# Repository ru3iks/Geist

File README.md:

<div align="center">

# GEIST

**A reference-grade balanced USB DAC, real-time DSP engine, and tactile media controller — designed and built from scratch.**

`ESP32-S3` · `PCM5102A` · `OPA1656` · `Rust` · `Tauri`

---

*24-bit · 96kHz · Balanced 4.4mm Pentaconn · 10-Band Parametric EQ · FFT Visualizer*

</div>

---

## What is Geist?

Geist is an open-source USB audio device that I designed from the ground up — the circuit, the PCB, the firmware, and the companion app. It plugs into a computer over USB-C and serves three functions simultaneously:

1. **Reference-Grade USB DAC** — Enumerates as a class-compliant USB Audio device (UAC1). Receives lossless 24-bit/96kHz audio, converts it through a hardware DAC, and drives headphones through a true balanced amplifier stage.

2. **Real-Time DSP Engine** — A 10-band parametric EQ processes audio in real-time on the ESP32-S3's vector DSP unit. An FFT spectrum visualizer renders live on the onboard display.

3. **Tactile Media Controller** — Physical rotary encoder, mechanical buttons, and a toggle switch send HID commands back to the PC for volume and playback control. No drivers needed.

The companion desktop app (built in Rust + Tauri) pushes track metadata and album art to the device, provides a graphical EQ editor, and displays real-time audio analysis.

> This project was built as a 2nd year B.Tech ECE student at Manipal Institute of Technology. Every part of it — analog circuit design, mixed-signal PCB layout, embedded Rust firmware, and desktop application — was learned and implemented from scratch.

---

## Hardware Architecture

### The Signal Chain

```
  USB-C ──► AP2112K (3.3V LDO) ──► ESP32-S3 ──► PCM5102A DAC ──► 2× OPA1656 ──► Headphones
       └──► LM27762 (±4.5V Charge Pump) ─────────────────────────────┘
```

Every component was selected to serve a specific role in the audio path:

| Block | Component | Role |
|---|---|---|
| **Power (Digital)** | AP2112K-3.3 | LDO regulator — steps 5V USB to clean 3.3V for all digital logic |
| **Power (Analog)** | LM27762 | Bipolar charge pump — generates ±4.5V dual rails for the op-amps |
| **Digital Brain** | ESP32-S3-WROOM-1 | Dual-core 240MHz processor — USB audio streaming, DSP, UI control |
| **DAC** | PCM5102A | 32-bit delta-sigma DAC — converts I2S digital audio to analog |
| **Amplifiers** | 2× OPA1656 | Ultra-low-noise dual op-amps — buffers and creates balanced output |
| **Display** | ST7789 (240×240) | SPI LCD — track info or FFT visualizer |
| **Input** | Alps EC11 + 3 push buttons + SPDT toggle | Volume/nav encoder, media keys, mode switch |
| **Output** | 4.4mm Pentaconn + 3.5mm TRS | True balanced and single-ended headphone outputs |

### The Life of an Audio Sample

This table traces a single sample from the moment it leaves the PC to the moment it moves air:

```
Step   Location                  Signal State                        Domain
─────────────────────────────────────────────────────────────────────────────
 1     PC audio engine           24-bit integer: 0x3FFFFF            Software
 2     USB cable (D+/D-)         NRZI-encoded differential packet    Digital
 3     ESP32 USB DMA buffer      Bytes in RAM                        Digital
 4     ESP32 I2S peripheral      Serial bitstream at 3.072 MHz       Digital (3.3V)
 5     PCM5102A delta-sigma      1-bit stream at 6.144 MHz           Digital
 6     PCM5102A OUTL pin         +2.05V (audio + 1.55V DC bias)      Analog
 7     OPA1656 buffer output     +2.05V → OUT_L+ (hot phase)         Analog
 8     OPA1656 inverter output   −0.50V → OUT_L− (cold phase)        Analog
 9     After 10Ω resistors       +2.04V / −0.49V                     Analog
 10    Headphone driver          ΔV = 2.53V differential → sound     Acoustic
```

### Why Balanced?

A balanced signal carries audio on two wires moving in opposite directions. Any noise that couples into the cable appears equally on both wires and is cancelled by subtraction at the receiver:

```
Single-Ended:                      Balanced:
Signal ── ╱╲╱~~╲╱╲ ── +V+noise     HOT  ── ╱╲╱~~╲╱╲ ── +V+noise
Ground ── ──────── ── 0V            COLD ── ╲╱╲~~╱╲╱ ── −V+noise

Amp sees: signal + noise            Amp subtracts: (+V+noise) − (−V+noise)
→ noise passes through ✗            = 2V signal, noise cancelled ✓
```

The OPA1656 op-amps create this balanced pair — one half buffers the DAC output (positive phase), the other half inverts it (negative phase, gain = −1).

---

## PCB Design Philosophy

Geist is laid out on a **2-layer PCB** with strict attention to analog/digital noise isolation:

```
◄──── DIGITAL ZONE ──────────►│◄──────── ANALOG ZONE ──────────►

┌──────────┐  ┌──────────────┐ │  ┌───────────┐  ┌───────────┐
│ ESP32-S3 │  │ Display,     │ │  │ OPA1656×2 │  │ Audio     │
│          │  │ Encoder,     │ │  │           │  │ Jacks     │
│          │  │ Buttons      │ │  │           │  │           │
└──────────┘  └──────────────┘ │  └───────────┘  └───────────┘
                               │
                         ┌─────┴─────┐
                         │ PCM5102A  │ ← sits on the border
                         └───────────┘

Bottom layer: UNBROKEN ground copper pour — no splits.
```

### Key Layout Rules

- **Zonal Segregation** — All digital components (ESP32, display, buttons) on one side. All analog components (op-amps, output jacks) on the other. The PCM5102A sits on the boundary with its digital input pins facing left and analog outputs facing right.

- **Solid Ground Plane** — No split grounds. A single unbroken copper pour on the bottom layer allows return currents to flow directly beneath their source traces (path of least inductance), minimizing loop area and radiated noise. This is the modern best practice endorsed by TI, Analog Devices, and EMC engineers — not the outdated "split and bridge" approach.

- **Tight Decoupling** — Every bypass capacitor is placed physically touching the power pins of its parent IC. A decoupling cap 15mm away is electrically useless — the trace inductance defeats its purpose.

- **Antenna Isolation** — The ESP32's Wi-Fi/Bluetooth antenna overhangs the board edge with a keepout zone beneath it. No copper, no traces, no components under the antenna.

---

## Firmware Architecture

The firmware is written in **Rust** using the Embassy async runtime — bare-metal, no RTOS, no garbage collector.

```
geist-firmware/
├── src/
│   ├── main.rs                ← Embassy entry, spawns all tasks
│   ├── usb/
│   │   ├── descriptors.rs     ← USB composite device (UAC1 + HID + CDC)
│   │   ├── audio.rs           ← Isochronous audio reception, buffer management
│   │   ├── hid.rs             ← Media key HID reports
│   │   └── cdc.rs             ← Serial link to companion app
│   ├── audio/
│   │   ├── i2s.rs             ← I2S DMA driver for PCM5102A
│   │   ├── buffer.rs          ← Lock-free ring buffer (USB → I2S)
│   │   └── dsp.rs             ← Biquad EQ engine + FFT analysis
│   ├── ui/
│   │   ├── display.rs         ← ST7789 SPI driver
│   │   ├── encoder.rs         ← EC11 rotary encoder with debounce
│   │   ├── buttons.rs         ← Debounced media buttons
│   │   └── renderer.rs        ← Track info view + spectrum visualizer
│   └── app/
│       └── state.rs           ← Global state machine
```

### USB Composite Device

Geist enumerates as three USB interfaces simultaneously — no custom drivers required:

| Interface | USB Class | Function |
|---|---|---|
| Audio Control + Audio Streaming | UAC1 | Appears as a sound card — receives PCM audio from the OS |
| HID (Consumer Control) | HID | Sends media keys (play/pause/next/prev) and volume from the encoder |
| CDC ACM | CDC | Virtual serial port for companion app communication |

### Real-Time DSP

The 10-band parametric EQ runs as a chain of biquad filters — each band is 5 multiplies and 4 adds per sample:

```rust
// One EQ band — runs for every sample, every channel
fn process(&mut self, x: f32) -> f32 {
    let y = self.b0 * x + self.b1 * self.x1 + self.b2 * self.x2
          - self.a1 * self.y1 - self.a2 * self.y2;
    self.x2 = self.x1; self.x1 = x;
    self.y2 = self.y1; self.y1 = y;
    y
}
```

At 48kHz stereo with 10 bands, this amounts to ~5 million operations per second — less than 2% of the ESP32-S3's capacity. The biquad coefficients are computed by the companion app from human-readable parameters (frequency, gain, Q) and sent over the CDC serial link.

### Task Model

```
Core 0 (Real-time audio — never blocked):
├── usb_audio_task()       ← Isochronous USB reception
├── i2s_feed_task()        ← Drains ring buffer → I2S DMA → PCM5102A
└── usb_hid_cdc_task()     ← HID reports + serial I/O

Core 1 (UI + DSP — lower priority):
├── dsp_task()             ← Biquad EQ processing + FFT analysis
├── display_task()         ← ST7789 rendering @ 30fps
└── input_task()           ← Encoder + button polling + debounce
```

---

## Companion App

Built with **Tauri** (Rust backend + web frontend) — a ~5MB native app, not a 150MB Electron wrapper.

### Features

- **Now Playing** — Reads track info from the OS media session (Windows SMTC / macOS MediaRemote / Linux MPRIS2) and pushes title, artist, and album art to Geist's display over CDC serial
- **10-Band Parametric EQ** — Interactive frequency response curve editor. Drag bands to set frequency, gain, and Q. Coefficients are computed locally and sent to the ESP32 in real-time
- **Real-Time Visualizer** — Captures system audio via loopback and renders spectrum analyzer, waveform, and spectrogram views in the browser frontend
- **Device Dashboard** — Connection status, sample rate, firmware version, output mode
- **System Tray** — Runs silently in the background, auto-connects when Geist is plugged in
- **Firmware Update** — Flash new firmware to the ESP32 over USB without opening the case
- **Listening Stats** — Tracks hours, volume levels, and session history in a local SQLite database

### Tech Stack

| Layer | Technology |
|---|---|
| Backend | Rust (serialport, windows-rs, cpal, rustfft, rusqlite) |
| Frontend | Svelte + HTML5 Canvas for visualizations |
| Framework | Tauri v2 |
| Protocol | JSON messages + binary RGB565 art over CDC serial |

---

## Bill of Materials

| Component | Part Number | Quantity | Description |
|---|---|---|---|
| MCU | ESP32-S3-WROOM-1 | 1 | Dual-core 240MHz, USB OTG, vector DSP |
| DAC | PCM5102A (PWR) | 1 | 32-bit delta-sigma, I2S input, 112dB SNR |
| Op-Amp | OPA1656IDR | 2 | Ultra-low-noise dual op-amp, 2.8 nV/√Hz |
| LDO | AP2112K-3.3TRG1 | 1 | 3.3V, 600mA, low-dropout regulator |
| Charge Pump | LM27762DSSR | 1 | Bipolar ±output from single supply |
| USB Connector | USB-C 16-pin | 1 | PCB-mount receptacle |
| Display | ST7789 240×240 | 1 | SPI TFT LCD module |
| Encoder | Alps EC11 | 1 | Rotary encoder with push switch |
| Toggle | SPDT | 1 | Mode select switch |
| Buttons | Tactile push | 3 | Prev / Play-Pause / Next |
| Balanced Jack | 4.4mm Pentaconn | 1 | Panel-mount, 5-pole |
| SE Jack | 3.5mm TRS | 1 | Panel-mount, 3-pole |
| Resistors | 0805 | 15 | Various values (see schematic) |
| Capacitors | 0805 | 15 | 0.1µF, 2.2µF, 4.7µF, 10µF |

---

## Project Structure

```
Geist/
├── hardware/                    ← KiCad project
│   ├── Geist.kicad_pro
│   ├── Geist.kicad_sch          ← Schematic
│   ├── Geist.kicad_pcb          ← PCB layout
│   └── fabrication/             ← Gerber files for manufacturing
│
├── firmware/                    ← ESP32-S3 Rust firmware
│   ├── Cargo.toml
│   └── src/
│
├── companion/                   ← Tauri desktop app
│   ├── src-tauri/               ← Rust backend
│   ├── src/                     ← Svelte frontend
│   └── package.json
│
├── enclosure/                   ← 3D-printable case (STEP/STL)
│
├── docs/
│   ├── hardware-signal-trace.md ← Complete electrical signal walkthrough
│   └── usb-audio-architecture.md← USB Audio Class deep dive
│
└── README.md
```

---

## Design Specifications

| Parameter | Value |
|---|---|
| Audio Format | PCM, 24-bit, 48kHz / 96kHz |
| USB Class | UAC1 (class-compliant, driverless) |
| DAC SNR | 112 dB (A-weighted) |
| DAC THD+N | −93 dB |
| Amp Noise | 2.8 nV/√Hz |
| Amp THD+N | −132 dB (0.000025%) |
| Output (Balanced) | 4.4mm Pentaconn, ~4 Vrms differential |
| Output (SE) | 3.5mm TRS |
| DSP | 10-band parametric EQ (biquad IIR) |
| Visualization | 1024-point FFT, real-time spectrum |
| Power | USB bus-powered (5V, <500mA) |
| PCB | 2-layer, solid ground plane |
| Firmware | Rust + Embassy (bare-metal async) |
| Companion App | Rust + Tauri + Svelte |

---

## Building

> 🚧 Build instructions will be added as each subsystem is completed.

### Hardware
1. Open `hardware/Geist.kicad_pro` in KiCad 9.0+
2. Generate Gerbers and order from JLCPCB or PCBWay (2-layer, 1.6mm, 1oz copper)
3. Source components from LCSC/Mouser/Digikey (see BOM above)
4. Hand-solder with hot air station (TSSOP/QFN packages) and soldering iron (0805 passives, connectors)

### Firmware
```bash
# Prerequisites: Rust toolchain + ESP32 target
rustup target add xtensa-esp32s3-none-elf
cargo install espflash

# Build and flash
cd firmware
cargo build --release
espflash flash target/xtensa-esp32s3-none-elf/release/geist-firmware
```

### Companion App
```bash
# Prerequisites: Rust, Node.js 18+, pnpm
cd companion
pnpm install
pnpm tauri dev     # development
pnpm tauri build   # production binary
```

---

## License

This project is open-source under the [MIT License](LICENSE).

---

<div align="center">

Designed and built by **Arihant** · MIT Manipal · 2026

*A project born from curiosity about what sits between the music and the ear.*

</div>

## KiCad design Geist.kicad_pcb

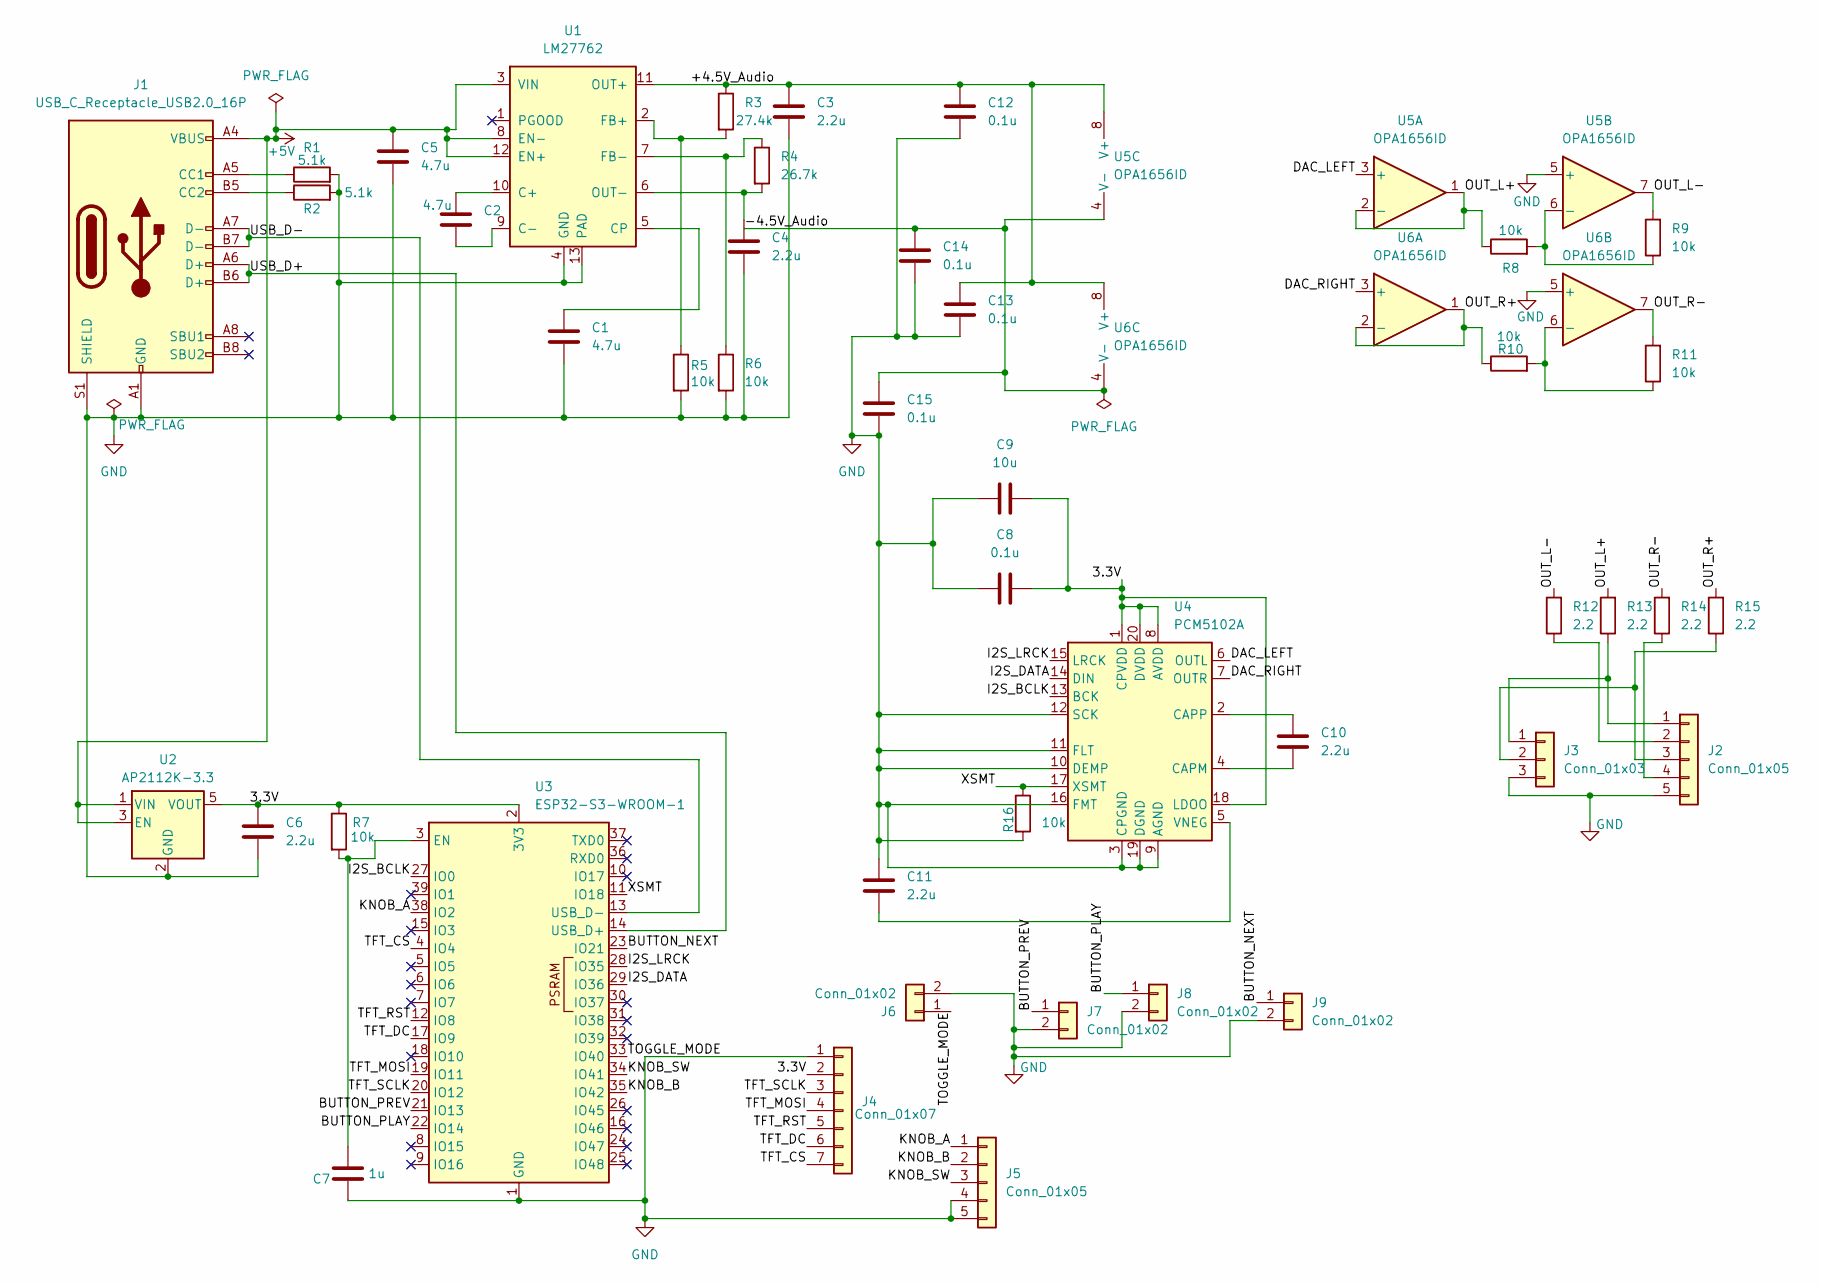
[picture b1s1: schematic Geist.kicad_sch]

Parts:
C1, C2, C5: 4.7u; C_0805_2012Metric_Pad1.18x1.45mm_HandSolder
C3, C4, C6, C10, C11: 2.2u; C_0805_2012Metric_Pad1.18x1.45mm_HandSolder
C7: 1u; C_0805_2012Metric_Pad1.18x1.45mm_HandSolder
C8, C12, C13, C14, C15: 0.1u; C_0805_2012Metric_Pad1.18x1.45mm_HandSolder
C9: 10u; C_0805_2012Metric_Pad1.18x1.45mm_HandSolder
J1: USB_C_Receptacle_USB2.0_16P; USB_C_Receptacle_HRO_TYPE-C-31-M-12
J2, J5: Conn_01x05; PinHeader_1x05_P2.54mm_Vertical
J3: Conn_01x03; PinHeader_1x03_P2.54mm_Vertical
J4: Conn_01x07; PinHeader_1x07_P2.54mm_Vertical
J6, J7, J8, J9: Conn_01x02; PinHeader_1x02_P2.54mm_Vertical
R1, R2: 5.1k; R_0805_2012Metric_Pad1.20x1.40mm_HandSolder
R3: 27.4k; R_0805_2012Metric_Pad1.20x1.40mm_HandSolder
R4: 26.7k; R_0805_2012Metric_Pad1.20x1.40mm_HandSolder
R5, R6, R7, R8, R9, R10, R11, R16: 10k; R_0805_2012Metric_Pad1.20x1.40mm_HandSolder
R12, R13, R14, R15: 2.2; R_0805_2012Metric_Pad1.20x1.40mm_HandSolder
U1: LM27762; WSON-12-1EP_3x2mm_P0.5mm_EP1x2.65_ThermalVias
U2: AP2112K-3.3; SOT-23-5
U3: ESP32-S3-WROOM-1
U4: PCM5102A; TSSOP-20_4.4x6.5mm_P0.65mm
U5, U6: OPA1656ID; SOIC-8_3.9x4.9mm_P1.27mm

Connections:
+5V: C5.1, J1.A4 (VBUS), J1.A9 (VBUS), J1.B4 (VBUS), J1.B9 (VBUS), U1.3 (VIN), U1.8 (EN-), U1.12 (EN+), U2.1 (VIN), U2.3 (EN)
/3.3V: C6.1, C8.2, C9.2, J4.2, R7.1, U2.5 (VOUT), U3.2 (3V3), U4.1 (CPVDD), U4.8 (AVDD), U4.18 (LDOO), U4.20 (DVDD)
/+4.5V_Audio: C3.1, C12.2, C13.2, R3.1, U1.11 (OUT+), U5.8 (V+), U6.8 (V+)
/-4.5V_Audio: C14.2, C15.2, U5.4 (V-), U6.4 (V-)
/BUTTON_NEXT: J9.1, U3.23 (IO21)
/BUTTON_PLAY: J8.1, U3.22 (IO14)
/BUTTON_PREV: J7.1, U3.21 (IO13)
/DAC_LEFT: U4.6 (OUTL), U5.3 (+)
/DAC_RIGHT: U4.7 (OUTR), U6.3 (+)
/I2S_BCLK: U3.27 (IO0), U4.13 (BCK)
/I2S_DATA: U3.29 (IO36), U4.14 (DIN)
/I2S_LRCK: U3.28 (IO35), U4.15 (LRCK)
/KNOB_A: J5.1, U3.38 (IO2)
/KNOB_B: J5.2, U3.35 (IO42)
/KNOB_SW: J5.3, U3.34 (IO41)
/OUT_L+: R8.1, R13.2, U5.1, U5.2 (-)
/OUT_L-: R9.2, R12.2, U5.7
/OUT_R+: R10.1, R15.2, U6.1, U6.2 (-)
/OUT_R-: R11.2, R14.2, U6.7
/TFT_CS: J4.7, U3.4 (IO4)
/TFT_DC: J4.6, U3.17 (IO9)
/TFT_MOSI: J4.4, U3.19 (IO11)
/TFT_RST: J4.5, U3.12 (IO8)
/TFT_SCLK: J4.3, U3.20 (IO12)
/TOGGLE_MODE: J6.1, U3.33 (IO40)
/USB_D+: J1.A6 (D+), J1.B6 (D+), U3.14 (USB_D+)
/USB_D-: J1.A7 (D-), J1.B7 (D-), U3.13 (USB_D-)
/XSMT: R16.1, U3.11 (IO18), U4.17 (XSMT)
GND: C1.2, C3.2, C4.2, C5.2, C6.2, C7.2, C8.1, C9.1, C11.2, C12.1, C13.1, C14.1, C15.1, J1.A1 (GND), J1.A12 (GND), J1.B1 (GND), J1.B12 (GND), J1.S1 (SHIELD), J2.5, J3.3, J4.1, J5.4, J5.5, J6.2, J7.2, J8.2, J9.2, R1.2, R2.2, R5.2, R6.2, R16.2, U1.4 (GND), U1.13 (PAD), U2.2 (GND), U3.1 (GND), U3.40 (GND), U3.41 (GND), U4.3 (CPGND), U4.9 (AGND), U4.10 (DEMP), U4.11 (FLT), U4.12 (SCK), U4.16 (FMT), U4.19 (DGND), U5.5 (+), U6.5 (+)
unnamed: J1.A5 (CC1), R1.1
unnamed: J1.B5 (CC2), R2.1
unnamed: J2.1, J3.1, R13.1
unnamed: J2.2, R12.1
unnamed: J2.3, J3.2, R15.1
unnamed: J2.4, R14.1
unnamed: C2.1, U1.10 (C+)
unnamed: C2.2, U1.9 (C-)
unnamed: C1.1, U1.5 (CP)
unnamed: R3.2, R5.1, U1.2 (FB+)
unnamed: R4.1, R6.1, U1.7 (FB-)
unnamed: C4.1, R4.2, U1.6 (OUT-)
unnamed: C7.1, R7.2, U3.3 (EN)
unnamed: C10.1, U4.4 (CAPM)
unnamed: C10.2, U4.2 (CAPP)
unnamed: C11.1, U4.5 (VNEG)
unnamed: R8.2, R9.1, U5.6 (-)
unnamed: R10.2, R11.1, U6.6 (-)

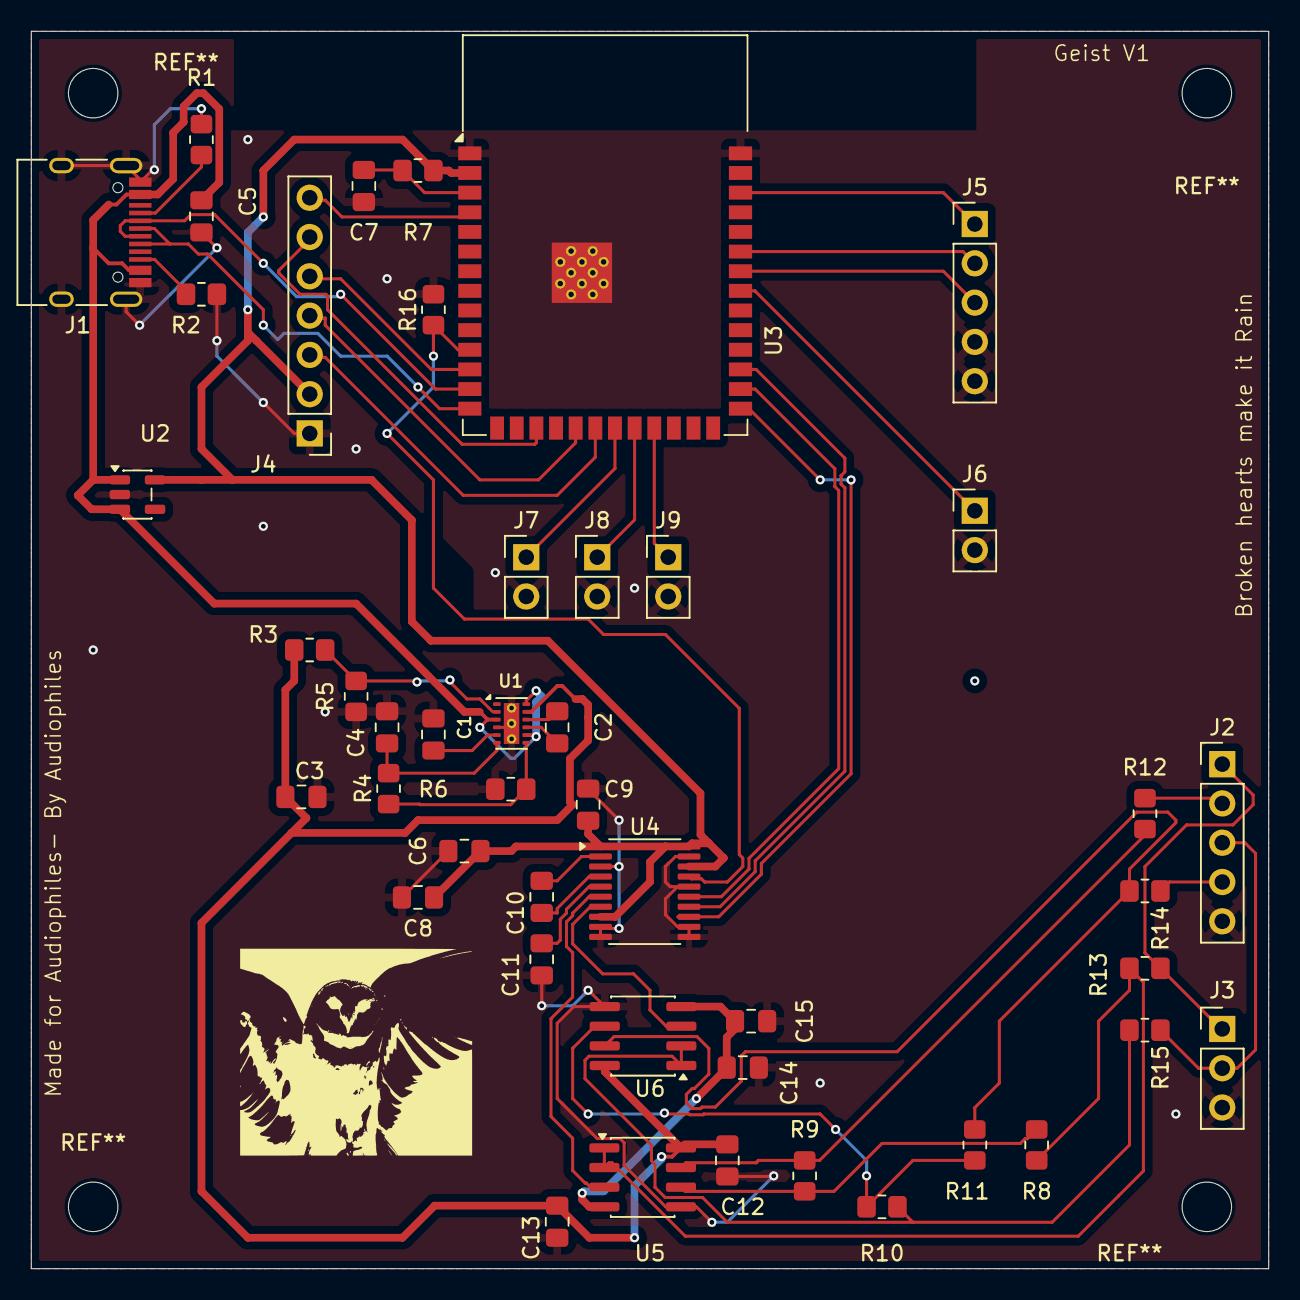
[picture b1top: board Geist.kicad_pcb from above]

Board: 2 copper layers, 80.0 x 80.0 mm, 46 parts (0 on the bottom side), 47 nets.

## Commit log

2026-06-05 GND pour
    laid gnd pour on the pcb and adjusted some pins to suit better routing. Will work on chopping down DRC next.
2026-06-06 DRC fixes
    further rectified DRC errors, now just need to add vias to thermal relief pads
2026-06-06 Adding reference pic for pcb
    adding a picture of almost-finished pcb design for future reference in case of changes.
2026-06-08 PCB Finished
    FIxed all DRCs and made further design decisions like making usb c connector hang 1mm off the edge. Added mounting holes. PCB finished. Will add bitmap in next commit.
2026-06-11 Started enclosure +electric_to_air
    started making enclosure in fusion 360 and board is fully finalised and rechecked multiple times. Added electric_to_air markdown file to explain the whole process start to finish.
